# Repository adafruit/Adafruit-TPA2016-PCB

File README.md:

# Adafruit Stereo 2.8W Class D Audio Amplifier TPA2016 PCB
<a href="http://www.adafruit.com/products/1712"><br/>
Click here to purchase one from the Adafruit shop</a>

A mini class D with AGC and I2C control? Yes please! This incredibly small stereo amplifier is surprisingly powerful. It is able to deliver 2 x 2.8W channels into 4 ohm impedance speakers (@ 10% THD) and it has a i2c control interface as well as an AGC (automatic gain control) system to keep your audio from clipping or distorting.

If you don't want to use I2C to control it, it does start up on with 6dB gain by default and the AGC set up for most music playing. We do suggest using it with a microcontroller to configure it, however, since its quite powerful. Settings are not stored in the chip, so you'll need to adjust any gain & AGC amplification settings every time the amp is powered up.

Inside the miniature chip is a class D controller, able to run from 2.7V-5.5VDC. Since the amp is a class D, it's incredibly efficient (89% efficient when driving an 8Ω speaker at 1.5 Watt) - making it perfect for portable and battery-powered projects. It has built in thermal and over-current protection but we could barely tell if it got hot. This board is a welcome upgrade to basic "LM386" amps!

PCB files for Adafruit TPA2016 I2C Audio Amplifier PCB. The format is EagleCAD schematic and board layout: https://www.adafruit.com/products/1712

### License

Adafruit invests time and resources providing this open source design, please support Adafruit and open-source hardware by purchasing products from [Adafruit](https://www.adafruit.com)!

All text above must be included in any redistribution

Designed by Limor Fried/Ladyada for Adafruit Industries.
Creative Commons Attribution/Share-Alike, all text above must be included in any redistribution. 
See license.txt for additional information.

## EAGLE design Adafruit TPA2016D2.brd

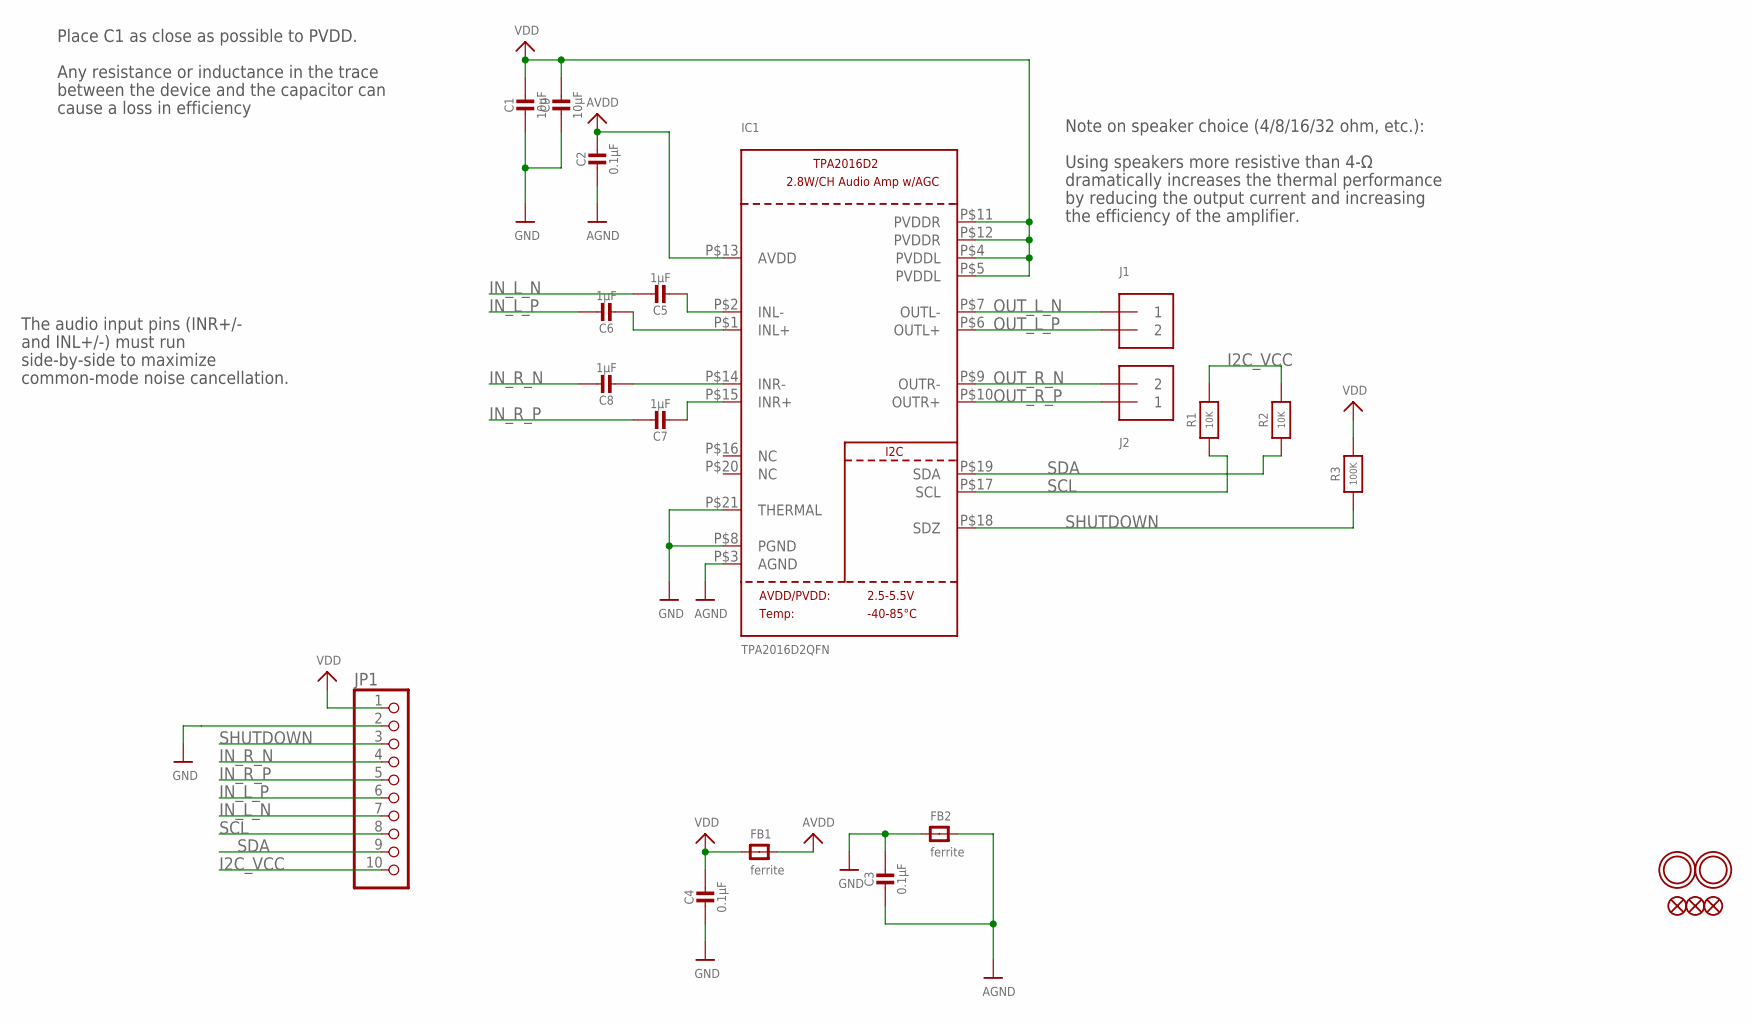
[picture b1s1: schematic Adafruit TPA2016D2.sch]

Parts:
C1, C9: 10µF; 0805-NO
C2, C3, C4: 0.1µF; 0805-NO
C5, C6, C7, C8: 1µF; 0805-NO
FB1, FB2: ferrite; _0805MP
FID1, FID2, FID3: FIDUCIAL""; FIDUCIAL_1MM
IC1: TPA2016D2QFN; QFN20_4MM
J1, J2: TERMBLOCK_1X2; TERMBLOCK_1X2-3.5MM
JP1: HEADER-1X1070MIL; 1X10_ROUND70
R1, R2: 10K; 0805-NO
R3: 100K; 0805-NO
U$20, U$21: MOUNTINGHOLE2.5_THICK; MOUNTINGHOLE_2.5_PLATED_THICK

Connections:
AGND: C2.2, C3.2, FB2.2, IC1.P$3 (AGND)
AVDD: C2.1, FB1.2, IC1.P$13 (AVDD)
GND: C1.2, C3.1, C4.2, C9.2, FB2.1, IC1.P$8 (PGND), IC1.P$21 (THERMAL), JP1.2
I2C_VCC: JP1.10, R1.2, R2.2
IN_L_N: C5.1, JP1.7
IN_L_P: C6.1, JP1.6
IN_R_N: C8.1, JP1.4
IN_R_P: C7.1, JP1.5
unnamed: C6.2, IC1.P$1 (INL+)
unnamed: C5.2, IC1.P$2 (INL-)
unnamed: C8.2, IC1.P$14 (INR-)
unnamed: C7.2, IC1.P$15 (INR+)
OUT_L_N: IC1.P$7 (OUTL-), J1.1
OUT_L_P: IC1.P$6 (OUTL+), J1.2
OUT_R_N: IC1.P$9 (OUTR-), J2.2
OUT_R_P: IC1.P$10 (OUTR+), J2.1
SCL: IC1.P$17 (SCL), JP1.8, R1.1
SDA: IC1.P$19 (SDA), JP1.9, R2.1
SHUTDOWN: IC1.P$18 (SDZ), JP1.3, R3.1
VDD: C1.1, C4.1, C9.1, FB1.1, IC1.P$4 (PVDDL), IC1.P$5 (PVDDL), IC1.P$11 (PVDDR), IC1.P$12 (PVDDR), JP1.1, R3.2

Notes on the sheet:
Place C1 as close as possible to PVDD.
Any resistance or inductance in the trace
between the device and the capacitor can
cause a loss in efficiency
Using speakers more resistive than 4-Ω
dramatically increases the thermal performance
by reducing the output current and increasing
the efficiency of the amplifier.
Note on speaker choice (4/8/16/32 ohm, etc.):
The audio input pins (INR+/-
and INL+/-) must run
side-by-side to maximize
common-mode noise cancellation.

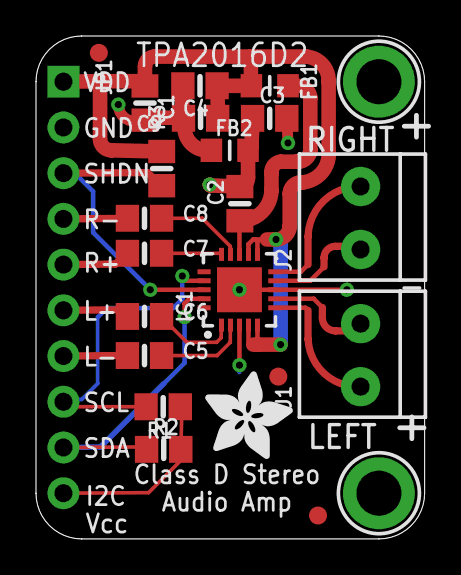
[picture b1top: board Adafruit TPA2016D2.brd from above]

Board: 2 copper layers, 21.6 x 27.9 mm, 25 parts (1 on the bottom side), 20 nets.

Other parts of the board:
U$3: ADAFRUIT_5MM
U$4: ADAFRUIT_3.5MM

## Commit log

2014-07-03 init!
2014-07-03 updated URL
